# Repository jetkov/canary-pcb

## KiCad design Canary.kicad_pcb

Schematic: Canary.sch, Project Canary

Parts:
C1, C2, C4, C8: 0.1u; C_0402_NoSilk; Part Number CL05A104KP5NNNC
C3, C9, C10: 1u; C_0402_NoSilk; Part Number CL05A105KP5NNNC
C5: DNP; C_0402_NoSilk; Part Number CL05A104KP5NNNC
C6, C7: 12pF; C_0402_NoSilk; Part Number CL05C120JB5NNNC
D1: GREEN; 155124xx73200; Part Number 155124VS73200
D2: YELLOW; 155124xx73200; Part Number 155124YS73200
D3: RED; 155124xx73200; Part Number 155124RS73200
D5, D6: D_Schottky_ALT; NSPU3051; Part Number NSPU3051N2T5G
FID1, FID2, FID3, FID4, FID5, FID6: Fiducial; Fiducial_1mm_Dia_2mm_Outer
H1, H2: MountingHole; MountingHole_2.2mm_M2
J1: CONN_ARM_CM_JTAG_SWD_10; 20021121-00010XXLFc; Part Number 20021121-00010T1LF
J2: 20021311-00010T4LF; Part Number 20021311-00010T4LF
LOGO1: CANARY-LOGO
LS1: PKMCS0909E4000-R1; Part Number PKMCS0909E4000-R1
Q1, Q3: PMN30UNX; PMN-NXP-TSOP6-SOT457; Part Number PMN30UNX
Q2: PMN42XPEAH; PMN-NXP-TSOP6-SOT457; Part Number PMN42XPEAH
R1: 2M; R_0402_NoSilk; Part Number RMCF0402FT2M00
R2: 2.4M; R_0402_NoSilk; Part Number RMCF0402FT2M40
R3, R5, R6: 180k; R_0402_NoSilk; Part Number RMCF0402FT180K
R4, R7: 10k; R_0402_NoSilk; Part Number RMCF0402FT10K0
R8, R9, R10, R11: 470R; R_0402_NoSilk; Part Number RMCF0402FT470R
R12: 499R; R_0402_NoSilk; Part Number RMCF0402FT499R
R30: 487k; R_0402_NoSilk; Part Number RMCF0402FT487K
S1: DNP; SM-UART-04L; Part Number SM-UART-04L
SW1: TL3301SPF160QJ; TL3301EF160QJ; Part Number TL3301SPF160QJ
TP1: TestPoint; Measurement_Point_Round-SMD-Pad_Small
U1: BMD-300-A-R; Part Number BMD-300-A-R
U2: DNP; MX25V1006FM1I; Part Number MX25V1006FM1I
U3: SHTC3; Part Number SHTC3
U4: SGP40; SGP40-D-R4; Part Number SGP40-D-R4
Y1: 32.7680 kHz; ECS-327-9-12-C-TR; Part Number ECS-.327-9-12-C-TR

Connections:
3V3_PS: U1.41 (P0.23); also elsewhere on the board
5V_EN: U1.6 (P0.25); also elsewhere on the board
+3V3: C3.1, C4.1, C5.1, J1.1 (VTref), SW1.1, SW1.2, U1.17 (VCC), U2.8 (VCC); also elsewhere on the board
+5V: J2.1, J2.2, Q2.4 (S), R6.1; also elsewhere on the board
+BATT: R1.2; also elsewhere on the board
/BAT_DIV: C1.1, R1.1, R2.1, U1.20 (P0.04/AIN2)
/NG: Q3.3 (G), R9.2
/PDRIVE: Q1.1 (D), Q1.2 (D), Q1.5 (D), Q1.6 (D), R6.2, R8.1, R9.1
/PDRIVE_O: D6.1, LS1.1, R30.2
/PG: Q2.3 (G), R8.2
/RBTN: D5.1, R3.1, R5.1, SW1.3, SW1.4
/XTAL1: C7.1, U1.13 (P0.00/XTAL1), Y1.2
/XTAL2: C6.2, U1.14 (P0.01/XTAL2), Y1.1
BUTTON: C2.1, R5.2, U1.37 (P0.19)
CHG_STAT: U1.40 (P0.22); also elsewhere on the board
I2C_SDA: R7.2, U1.28 (P0.12), U3.3 (SDA), U4.3 (SDA); also elsewhere on the board
LED_AMBER: D2.2 (A), U1.23 (P0.07)
LED_GREEN: D1.2 (A), U1.24 (P0.08)
LED_RED: D3.2 (A), U1.22 (P0.06)
LMP_VOUT_B: U1.21 (P0.05/AIN3); also elsewhere on the board
unnamed: D1.1 (K), R10.1
unnamed: D2.1 (K), R11.1
unnamed: D3.1 (K), R12.1
unnamed: Q2.1 (D), Q2.2 (D), Q2.5 (D), Q2.6 (D), Q3.1 (D), Q3.2 (D), Q3.5 (D), Q3.6 (D), R30.1
unnamed: TP1.1, U1.19 (P0.03/AIN1)
PIEZO_PWM: Q1.3 (G), U1.12 (P0.31)
PM_UART_RXD: J2.7, U1.25 (P0.09/NFC1)
PM_UART_TXD: J2.9, U1.26 (P0.10/NFC2)
SPI_CLK: U1.32 (P0.14/TRACEDATA[3]), U2.6 (SCLK)
SPI_MISO: U1.34 (P0.16/TRACEDATA[1]), U2.2 (SO/SIO1)
SPI_MOSI: U1.33 (P0.15/TRACEDATA[2]), U2.5 (SI/SDO0)
SWDCLK: J1.4 (SWDCLK/TCK), U1.44 (SWDIO)
SWDIO: J1.2 (SWDIO/TMS), U1.43 (SWCLK)
SWO: J1.6 (SWO/TDO), U1.36 (P0.18/TRACEDATA[0]/SWO)
VDD: C8.1, C9.1, C10.1, R4.1, R7.1, U3.1 (VDD), U4.1 (VDD), U4.5 (VDDH); also elsewhere on the board
VDD_EN: U1.42 (P0.24); also elsewhere on the board
VREF_EN: U1.7 (P0.26); also elsewhere on the board
~FLASH_CS~: U1.35 (P0.17), U2.1 (~CS~)
~LMP_EN~: U1.8 (P0.27); also elsewhere on the board
~PM_RST~: J2.5, U1.38 (P0.20/TRACECLK)
~PM_SLEEP~: J2.10, U1.27 (P0.11)
~RESET~: J1.10 (~RESET~), U1.39 (P0.21/~RESET)

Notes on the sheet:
Indication
VOC Sensor
Humidity + Temperature Sensor
Address: 0x59 Freq: 0 to 100kHz 0 to 400kHz
Address: 0x70 Freq: 0 to 1MHz
NOR Flash
PM Sensor Connector
Shutdown Iq: 34uA typ, 105uA max Run: 2.6mA typ, 3mA max
Shutdown Iq: 1uA typ, 10uA max Run: 5mA typ, 20mA max
P0.22-0.31 low drive, low frequency only
Shutdown Iq: ~5mA Run: 60mA typ, 100mA max
Shutdown Iq: 0.3uA typ, 0.6uA max Run: 430uA typ, 900uA max
Shutdown Iq: 0.3uA typ, 1.2uA max Run: 3.3mA typ
nRF52832
SWD Connector
MCU + BLE
Sensors
Sleep Total Iq: (2+1+7+1.2+10)uA/85% + 5uA = 30uA max Sensor/Comm Duty Cycle: 15s/(10*60s) = 2.5% Run Total: 3.3V: [3.3mA + (2.5%)(2.6+5+0.5+0.5)mA]/85% = 5mA max 5.0V: (2.5%)(100+0.5)mA/85% = 3mA max -> 5mA @ 3.3V
Power Consumption Rough Max Estimates
6 months sleep: 6*30*24h * (30e-3)mA = 130mAh 3 days run: 3*24h * 10mA = 720mAh Max Total: 850mAh Est. Realistic Total: 500mAh
C1 = C2 = 2(C_L - C_stray) C1 = C2 = 2(9-3) = 12pF
4.4V -> 2.4V
GPIO Specifications Vmin = -0.3V, Vmax = VCC+0.3V = 3.9V Vih = 0.7 * VCC = 2.31V Vil = 0.3 * VCC = 0.99V
Button
Vf @ 3mA = 1.9V Intensity = 8 mcd
Vf @ 3mA = 1.9V Intensity = 20 mcd
Vf @ 3mA = 1.8V Intensity = 20 mcd
Assume 20pF capacitance 4kHz -> 250us = 20T 250us / 20 = RC -> R = 625k
Pizeo Buzzer

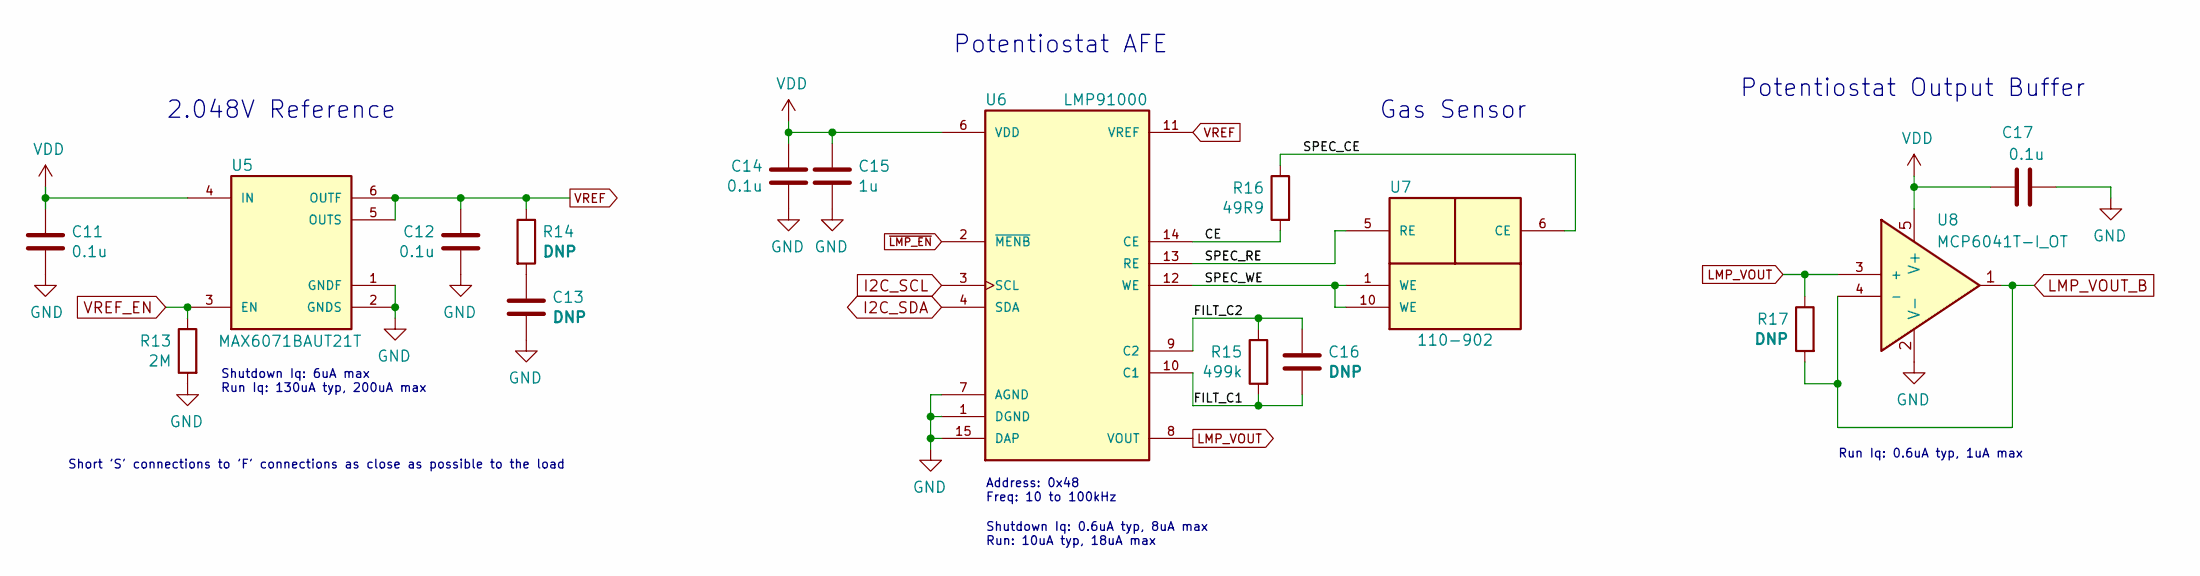
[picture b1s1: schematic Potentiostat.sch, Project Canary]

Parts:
C11, C12, C14, C17: 0.1u; C_0402_NoSilk; Part Number CL05A104KP5NNNC
C13, C16: DNP; C_0402_NoSilk
C15: 1u; C_0402_NoSilk; Part Number CL05A105KP5NNNC
R13: 2M; R_0402_NoSilk; Part Number RMCF0402FT2M00
R14, R17: DNP; R_0402_NoSilk
R15: 499k; R_0402_NoSilk; Part Number RMCF0402FT499K
R16: 49R9; R_0402_NoSilk; Part Number RMCF0402FT49R9
U5: MAX6071BAUT21T; MAX6071BAUT21; Part Number MAX6071BAUT21+T
U6: LMP91000; Part Number LMP91000SD/NOPB
U7: 110-902; SPEC-110-902; Part Number 110-902
U8: MCP6041T-I_OT; Part Number MCP6041T-I/OT

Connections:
/Potentiostat/CE: R16.2, U6.14 (CE)
/Potentiostat/FILT_C1: C16.2, R15.2, U6.10 (C1)
/Potentiostat/FILT_C2: C16.1, R15.1, U6.9 (C2)
/Potentiostat/SPEC_CE: R16.1, U7.6 (CE)
/Potentiostat/SPEC_RE: U6.13 (RE), U7.5 (RE)
/Potentiostat/SPEC_WE: U6.12 (WE), U7.1 (WE), U7.10 (WE)
I2C_SDA: U6.4 (SDA); also elsewhere on the board
LMP_VOUT: R17.1, U6.8 (VOUT), U8.3 (+)
LMP_VOUT_B: R17.2, U8.1, U8.4 (-); also elsewhere on the board
unnamed: C13.1, R14.2
VDD: C11.1, C14.1, C15.1, C17.1, U5.4 (IN), U6.6 (VDD), U8.5 (V+); also elsewhere on the board
VREF: C12.1, R14.1, U5.5 (OUTS), U5.6 (OUTF), U6.11 (VREF)
VREF_EN: R13.1, U5.3 (EN); also elsewhere on the board
~LMP_EN~: U6.2 (~MENB); also elsewhere on the board

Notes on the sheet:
Address: 0x48 Freq: 10 to 100kHz
Potentiostat AFE
2.048V Reference
Potentiostat Output Buffer
Shutdown Iq: 6uA max Run Iq: 130uA typ, 200uA max
Shutdown Iq: 0.6uA typ, 8uA max Run: 10uA typ, 18uA max
Run Iq: 0.6uA typ, 1uA max
Gas Sensor
Short 'S' connections to 'F' connections as close as possible to the load

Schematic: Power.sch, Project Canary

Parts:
C18, C20: 10u; C_0603; Part Number CL10A106MP8NNNC
C19, C23, C26: 1u; C_0402_NoSilk; Part Number CL05A105KP5NNNC
C21, C24: 4.7u; C_0402_NoSilk; Part Number CL05A475MP5NRNC
C22, C25: 22u; C_0603; Part Number GRM188R61A226ME15D
D4: D_Schottky; PMEG2010EA; Part Number PMEG2010EA,135
D7: D_Schottky_ALT; NSPU3051; Part Number NSPU3051N2T5G
J3: USB4125-GF-A; Part Number USB4125-GF-A
J4: S2B-PH-SM4-TB; JST_S2B-PH-SM4-TB; Part Number S2B-PH-SM4-TB(LF)(SN)
L1: 2.2u; MAMK2520T2R2M; Part Number MAMK2520T2R2M
L2: 4.7u; LQH3NPZ4R7MMEL; Part Number LQH3NPZ4R7MMEL
R18, R26: 2M; R_0402_NoSilk; Part Number RMCF0402FT2M00
R19, R20: 5.1k; R_0402_NoSilk; Part Number RMCF0402FT5K10
R21: 487k; R_0402_NoSilk; Part Number RMCF0402FT487K
R22: 86.6k; R_0402_NoSilk; Part Number RMCF0402FT86K6
R23: 300k; R_0402_NoSilk; Part Number RMCF0402FT300K
R24: 180k; R_0402_NoSilk; Part Number RMCF0402FT180K
R25: 0R; R_0402_NoSilk; Part Number RMCF0402ZT0R00
R27: 10k; R_0402_NoSilk; Part Number RMCF0402FT10K0
R28: 9.1k; R_0402_NoSilk; Part Number RMCF0402FT9K10
R29: 3k; R_0402_NoSilk; Part Number RMCF0402FT3K00
U9: RT6150AGQW; Part Number RT6150AGQW
U10: LP5907MFX-3.2; LP5907MFX; Part Number LP5907MFX-3.2/NOPB
U11: MCP73831T-2ATI_OT; MCP7383xx-xxxx_OT; Part Number MCP73831T-2ATI/OT
U12: MIC2288YD5; Part Number MIC2288YD5-TR

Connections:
3V3_PS: R18.1, U9.7 (PS); also elsewhere on the board
5V_EN: R26.1, U12.4 (EN); also elsewhere on the board
+3V3: C19.1, C20.1, R21.1, R25.2, U9.1 (VOUT), U10.1 (IN); also elsewhere on the board
+5V: C25.1, C26.1, D4.1 (K), R28.1; also elsewhere on the board
+BATT: C18.1, C22.1, C24.1, J4.1, L2.1, U9.5 (VIN), U9.6 (EN), U9.8 (VINA), U11.3 (VBAT), U12.5 (VIN); also elsewhere on the board
/Power/CPR: R27.1, U11.5 (PROG)
/Power/CST: R24.2, U11.1 (STAT)
/Power/HVR_FB: R28.2, R29.1, U12.3 (FB)
/Power/HVR_SW: D4.2 (A), L2.2, U12.1 (SW)
/Power/LVR_FB: R21.2, R22.1, U9.10 (FB)
/Power/LVR_LX1: L1.1, U9.4 (LX1)
/Power/LVR_LX2: L1.2, U9.2 (LX2)
/Power/USB_CC1: J3.A5 (CC1), R20.1
/Power/USB_CC2: J3.B5 (CC2), R19.1
CHG_STAT: R23.1, R24.1; also elsewhere on the board
VBUS: C21.1, D7.1, J3.A9 (VBUS), J3.B9 (VBUS), U11.4 (VDD)
VDD: C23.1, R25.1, U10.5 (OUT); also elsewhere on the board
VDD_EN: U10.3 (EN); also elsewhere on the board

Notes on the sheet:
Rprog (k) = 1000 (V) / Ireg (mA) 10k -> 100mA 2k -> 500mA
Buck/Boost Converter
Vref = 1.24V R2 <= 5k R1/R2 = (Vout/Vref) - 1 = 3.0323 R1 = 3.09k or 9.1k, R2 = 1.02k or 3k 85% > D = 1-(Vin/Vout) =1-(3/5) = 0.4 Recommended L @ 5V = 4.7uH Vo < 6V -> Cout = 22uF = Cin
Boost Converter
Li-ion Charger
Li-ion Battery
USB C
Battery
3.2V LDO
Power Regulation
PS: Pull low for power save mode and pull high for fixed switching frequency operation. Efficiency: 85% @ 1-3mA PSM 25% @ 1-3mA FFM
R1 = 487k Fb = 500mV R2 = R1 / (Vout/Fb - 1) = 86.964k Cff = [(487k/R1) * 20] -20 (pF) = 0 pF L = 2.2uH @ 3.3Vo & 2.5-4.2Vin [1.5uH < L < 4.7uH] Cin & Cout recommended -> 10μF/X7R/1206
Shutdown Iq: 0.1uA typ, 1uA max Run efficiency: 85% (-0.5mA res div)
Shutdown Iq: 0.1uA typ, 2uA max
Internal 1M pull-down on EN
Shutdown Iq: 0.2uA typ, 1uA max Run Iq: 250uA typ, 425uA max @ 250mA
5.2V -> 3.25V

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
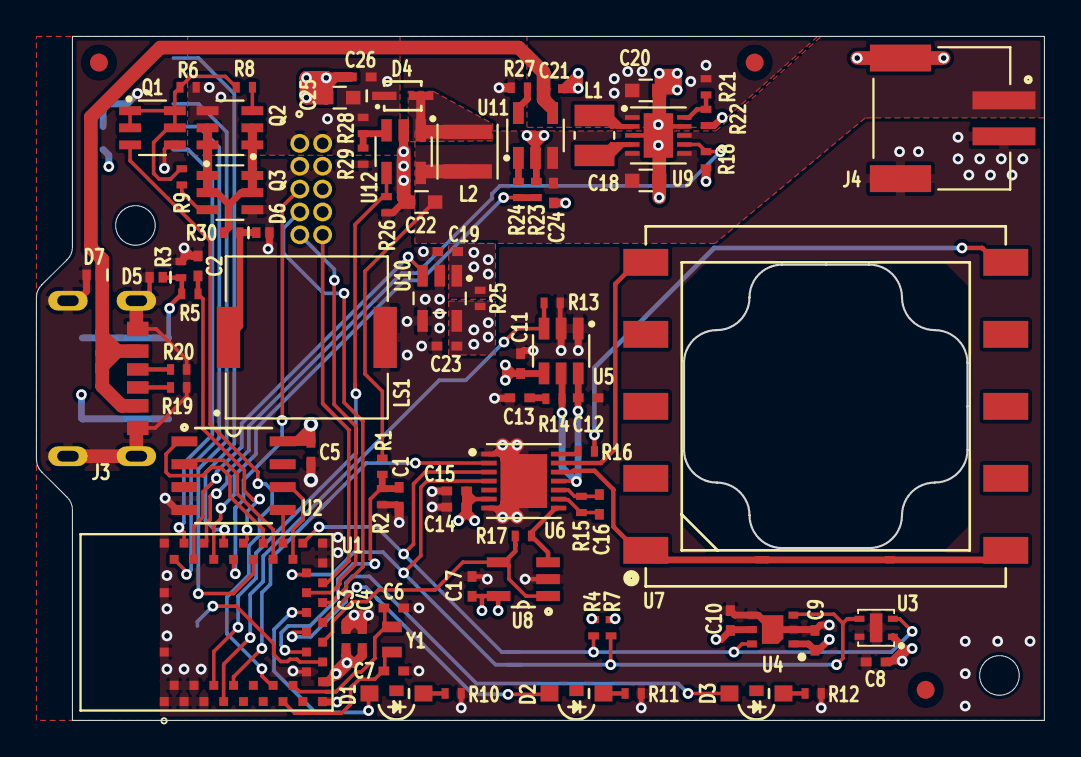
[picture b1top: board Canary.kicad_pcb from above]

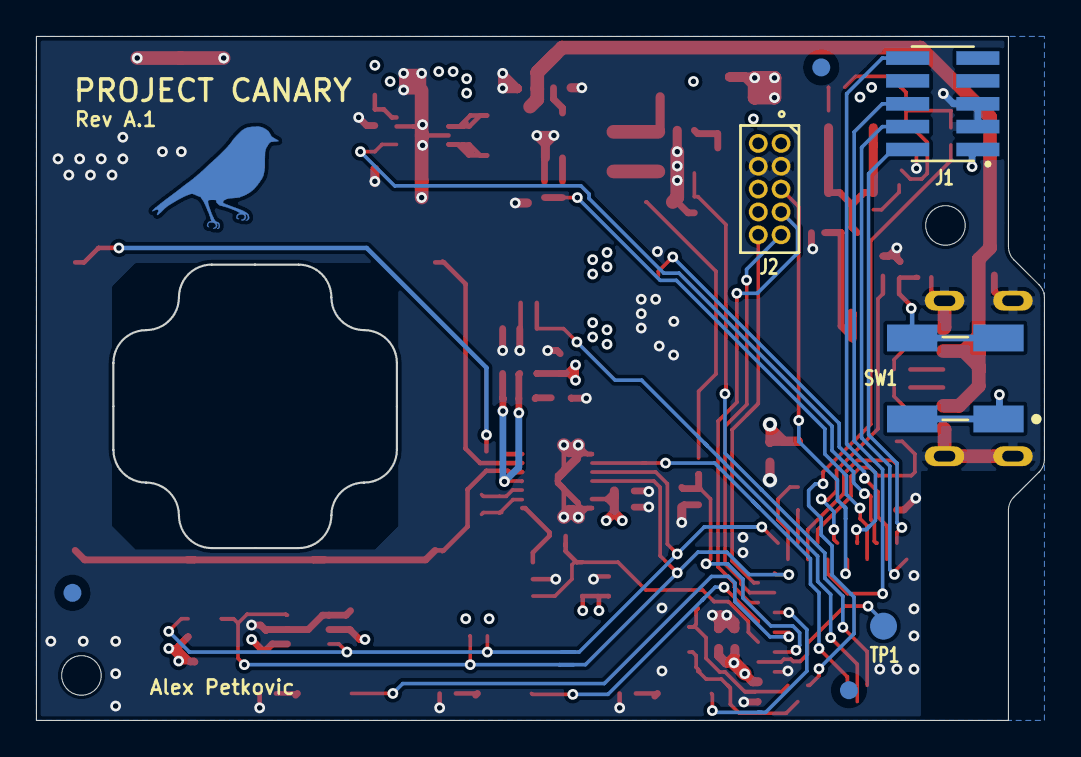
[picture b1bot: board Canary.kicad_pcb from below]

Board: 4 copper layers, 55.9 x 37.9 mm, 98 parts (8 on the bottom side), 63 nets.

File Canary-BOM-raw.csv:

"Reference(s)","Value","Qty","Part Number","Manufacturer","Description","Footprint"
"C1, C2, C4, C8, C11, C12, C14, C17","0.1u","8","CL05A104KP5NNNC","Samsung Electro-Mechanics","CAP CER 0.1UF 10V X5R 0402","JetkovKiCADLib:C_0402_NoSilk"
"C3, C9, C10, C15, C19, C23, C26","1u","7","CL05A105KP5NNNC","Samsung Electro-Mechanics","CAP CER 1UF 10V X5R 0402","JetkovKiCADLib:C_0402_NoSilk"
"C6, C7","12pF","2","CL05C120JB5NNNC","Samsung Electro-Mechanics","CAP CER 12PF 50V C0G/NP0 0402","JetkovKiCADLib:C_0402_NoSilk"
"C18, C20","10u","2","CL10A106MP8NNNC","Samsung Electro-Mechanics","CAP CER 10UF 10V X5R 0603","JetkovKiCADLib:C_0603"
"C21, C24","4.7u","2","CL05A475MP5NRNC","Samsung Electro-Mechanics","CAP CER 4.7UF 10V X5R 0402","JetkovKiCADLib:C_0402_NoSilk"
"C22, C25","22u","2","GRM188R61A226ME15D","Murata Electronics","CAP CER 22UF 10V X5R 0603","JetkovKiCADLib:C_0603"
"D1","GREEN","1","155124VS73200","Wurth Elektronik","LED GREEN CLEAR 1204 SMD R/A","JetkovKiCADLib:155124xx73200"
"D2","YELLOW","1","155124YS73200","Wurth Elektronik","LED YELLOW CLEAR 1204 SMD R/A","JetkovKiCADLib:155124xx73200"
"D3","RED","1","155124RS73200","Wurth Elektronik","LED RED CLEAR 1204 SMD R/A","JetkovKiCADLib:155124xx73200"
"D4","D_Schottky","1","PMEG2010EA,135","Nexperia USA Inc.","DIODE SCHOTTKY 20V 1A SOD323","JetkovKiCADLib:PMEG2010EA"
"D5, D6, D7","D_Schottky_ALT","3","NSPU3051N2T5G","ON Semiconductor","TVS DIODE 5.5V 9.5V 2X2DFN","JetkovKiCADLib:NSPU3051"
"J1","CONN_ARM_CM_JTAG_SWD_10","1","20021121-00010T1LF","Amphenol ICC (FCI)","CONN HEADER SMD 10POS 1.27MM","JetkovKiCADLib:20021121-00010XXLFc"
"J2","20021311-00010T4LF","1","20021311-00010T4LF","Amphenol ICC (FCI)","CONN RCPT 10POS 0.05 GOLD PCB","JetkovKiCADLib:20021311-00010T4LF"
"J3","USB4125-GF-A","1","USB4125-GF-A","GCT","USB C REC, GF, RA, 6P, SMT, TH S","JetkovKiCADLib:USB4125-GF-A"
"J4","S2B-PH-SM4-TB","1","S2B-PH-SM4-TB(LF)(SN)","JST Sales America Inc.","CONN HEADER SMD R/A 2POS 2MM","JetkovKiCADLib:JST_S2B-PH-SM4-TB"
"L1","2.2u","1","MAMK2520T2R2M","Taiyo Yuden","FIXED IND 2.2UH 1.9A 117 MOHM","JetkovKiCADLib:MAMK2520T2R2M"
"L2","4.7u","1","LQH3NPZ4R7MMEL","Murata Electronics","FIXED IND 4.7UH 1A 120 MOHM SMD","JetkovKiCADLib:LQH3NPZ4R7MMEL"
"LS1","PKMCS0909E4000-R1","1","PKMCS0909E4000-R1","Murata Electronics","AUDIO PIEZO TRANSDUCER 12.5V SMD","JetkovKiCADLib:PKMCS0909E4000-R1"
"Q1, Q3","PMN30UNX","2","PMN30UNX","Nexperia USA Inc.","MOSFET N-CH 30V 4.5A 6TSOP","JetkovKiCADLib:PMN-NXP-TSOP6-SOT457"
"Q2","PMN42XPEAH","1","PMN42XPEAH","Nexperia USA Inc.","MOSFET P-CH 20V 5.7A 6TSOP","JetkovKiCADLib:PMN-NXP-TSOP6-SOT457"
"R1, R13, R18, R26","2M","4","RMCF0402FT2M00","Stackpole Electronics Inc","RES 2M OHM 1% 1/16W 0402","JetkovKiCADLib:R_0402_NoSilk"
"R2","2.4M","1","RMCF0402FT2M40","Stackpole Electronics Inc","RES 2.4M OHM 1% 1/16W 0402","JetkovKiCADLib:R_0402_NoSilk"
"R3, R5, R6, R24","180k","4","RMCF0402FT180K","Stackpole Electronics Inc","RES 180K OHM 1% 1/16W 0402","JetkovKiCADLib:R_0402_NoSilk"
"R4, R7, R27","10k","3","RMCF0402FT10K0","Stackpole Electronics Inc","RES 10K OHM 1% 1/16W 0402","JetkovKiCADLib:R_0402_NoSilk"
"R8, R9, R10, R11","470R","4","RMCF0402FT470R","Stackpole Electronics Inc","RES 470 OHM 1% 1/16W 0402","JetkovKiCADLib:R_0402_NoSilk"
"R12","499R","1","RMCF0402FT499R","Stackpole Electronics Inc","RES 499 OHM 1% 1/16W 0402","JetkovKiCADLib:R_0402_NoSilk"
"R15","499k","1","RMCF0402FT499K","Stackpole Electronics Inc","RES 499K OHM 1% 1/16W 0402","JetkovKiCADLib:R_0402_NoSilk"
"R16","49R9","1","RMCF0402FT49R9","Stackpole Electronics Inc","RES 49.9 OHM 1% 1/16W 0402","JetkovKiCADLib:R_0402_NoSilk"
"R19, R20","5.1k","2","RMCF0402FT5K10","Stackpole Electronics Inc","RES 5.1K OHM 1% 1/16W 0402","JetkovKiCADLib:R_0402_NoSilk"
"R21, R30","487k","2","RMCF0402FT487K","Stackpole Electronics Inc","RES 487K OHM 1% 1/16W 0402","JetkovKiCADLib:R_0402_NoSilk"
"R22","86.6k","1","RMCF0402FT86K6","Stackpole Electronics Inc","RES 86.6K OHM 1% 1/16W 0402","JetkovKiCADLib:R_0402_NoSilk"
"R23","300k","1","RMCF0402FT300K","Stackpole Electronics Inc","RES 300K OHM 1% 1/16W 0402","JetkovKiCADLib:R_0402_NoSilk"
"R25","0R","1","RMCF0402ZT0R00","Stackpole Electronics Inc","RES 0 OHM JUMPER 1/16W 0402","JetkovKiCADLib:R_0402_NoSilk"
"R28","9.1k","1","RMCF0402FT9K10","Stackpole Electronics Inc","RES 9.1K OHM 1% 1/16W 0402","JetkovKiCADLib:R_0402_NoSilk"
"R29","3k","1","RMCF0402FT3K00","Stackpole Electronics Inc","RES 3K OHM 1% 1/16W 0402","JetkovKiCADLib:R_0402_NoSilk"
"SW1","TL3301SPF160QJ","1","TL3301SPF160QJ","E-Switch","SWITCH TACTILE SPST-NO 0.05A 12V","JetkovKiCADLib:TL3301EF160QJ"
"U1","BMD-300-A-R","1","BMD-300-A-R","U-Blox","RX TXRX MOD BLE 5.0 NORDIC SMD","JetkovKiCADLib:BMD-300-A-R"
"U3","SHTC3","1","SHTC3","Sensirion AG","SENSOR HUMI/TEMP I2C 2% SMD","JetkovKiCADLib:SHTC3"
"U4","SGP40","1","SGP40-D-R4","Sensirion AG","AIR QUALITY GAS SENSOR FOR VOC'S","JetkovKiCADLib:SGP40-D-R4"
"U5","MAX6071BAUT21T","1","MAX6071BAUT21+T","Maxim Integrated","IC VREF SERIES 0.08% SOT23-6","JetkovKiCADLib:MAX6071BAUT21"
"U6","LMP91000","1","LMP91000SD/NOPB","Texas Instruments","IC AFE 1 CHAN 8BIT 14WSON","JetkovKiCADLib:LMP91000"
"U7","110-902","1","110-902","SPEC Sensors, LLC","SENS GAS AIR QUAL ANALG CUR MOD","JetkovKiCADLib:SPEC-110-902"
"U8","MCP6041T-I_OT","1","MCP6041T-I/OT","Microchip Technology","IC OPAMP GP 1 CIRCUIT SOT23-5","JetkovKiCADLib:MCP6041T-I_OT"
"U9","RT6150AGQW","1","RT6150AGQW","Richtek USA Inc.","IC REG BCK BST ADJ 800MA 10WDFN","JetkovKiCADLib:RT6150AGQW"
"U10","LP5907MFX-3.2","1","LP5907MFX-3.2/NOPB","Texas Instruments","IC REG LINEAR 3.2V 250MA SOT23-5","JetkovKiCADLib:LP5907MFX"
"U11","MCP73831T-2ATI_OT","1","MCP73831T-2ATI/OT","Microchip Technology","IC BATT CNTL LI-ION 1CEL SOT23-5","JetkovKiCADLib:MCP7383xx-xxxx_OT"
"U12","MIC2288YD5","1","MIC2288YD5-TR","Microchip Technology","IC REG BOOST ADJ 1.2A TSOT23-5","JetkovKiCADLib:MIC2288YD5"
"Y1","32.7680 kHz","1","ECS-.327-9-12-C-TR","ECS Inc.","CRYSTAL 32.7680KHZ 9PF 10PPM SMD","JetkovKiCADLib:ECS-327-9-12-C-TR"

"C5, C13, C16","DNP","3","CL05A104KP5NNNC","Samsung Electro-Mechanics","CAP CER 0.1UF 10V X5R 0402","JetkovKiCADLib:C_0402_NoSilk"
"FID1, FID2, FID3, FID4, FID5, FID6","Fiducial","6","","","","Fiducials:Fiducial_1mm_Dia_2mm_Outer"
"H1, H2","MountingHole","2","~","~","~","Mounting_Holes:MountingHole_2.2mm_M2"
"LOGO1","CANARY-LOGO","1","","","","JetkovKiCADLib:CANARY-LOGO"
"R14, R17","DNP","2","~","~","~","JetkovKiCADLib:R_0402_NoSilk"
"S1","DNP","1","SM-UART-04L","Amphenol Advanced Sensors","PM2.5 IR LASER DUST SENSOR","JetkovKiCADLib:SM-UART-04L"
"U2","DNP","1","MX25V1006FM1I","Macronix","IC FLASH 1MBIT SPI/DUAL I/O 8SOP","JetkovKiCADLib:MX25V1006FM1I"

"Source:","C:\Users\Alex\Documents\KiCAD\Canary\Canary.sch"
"Date:","2021-03-02 04:31:07"
"Tool:","Eeschema (5.1.9)-1"
"Generator:","C:\Users\Alex\Documents\KiCAD\JetkovKiCADLib\Scripts/jetkov_bom_csv.py"
"Component Count:","97"

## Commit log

2021-02-24 Init
2021-02-24 Cleanup
2021-02-24 Clean up, add notes
2021-02-24 Select caps
2021-02-24 cleanup, add inductors
2021-02-24 Add diode info
2021-02-24 Add pizeo
2021-02-24 remove cache
2021-02-24 Fix part info, start rough layout
2021-02-24 Update ignore
2021-02-27 Adjust layour
2021-02-28 Update switch, placement adjustments
2021-02-28 Update switch
2021-02-28 Almost final main component placement
2021-02-28 Board setup and rules
2021-02-28 group components
2021-02-28 Clean up schem, wire in button
2021-02-28 Spec LED resistors
2021-02-28 Review
2021-02-28 Resolve DRC errors and add proper flagging
2021-02-28 Review everything, ready for layout
2021-03-01 Reannotate, fix BMD reference
2021-03-01 layout wip
2021-03-01 routing wip
2021-03-01 Add resistor details
2021-03-01 Fill in component info, reduce uniqe resistors. cleanup
2021-03-01 Info tweaks
2021-03-02 Routing done (needs review)
2021-03-02 Resolve DRC errors
2021-03-02 Change crystal
2021-03-02 Change crystal again
2021-03-02 Add canary logo
2021-03-02 Add TVS diodes, resistor for piezo drive, and test point
2021-03-02 Add TVS diodes, piezo resistor, testpoint, cleanup
2021-03-02 Clean up silks, add fiducials
2021-03-02 Tweak component infos
2021-03-02 Prepare for fab export
2021-03-02 Generate gerbers
2021-03-02 Regenerate Gerbers using PCBWay process
2021-03-02 Clean up silk, add page info
2021-03-02 Cleanup tracks/vias
2021-03-02 Make USB conn SMD part, add paste to THP
2021-03-02 Rerun gerber export
2021-03-02 Set logo virtual
2021-03-02 Gerber zips
2022-01-06 Final

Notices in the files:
parts and their libraries:
Copyright 2016 Accelerated Designs. All rights reserved.
